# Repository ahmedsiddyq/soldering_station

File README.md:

# Soldering Station

DIY electronic soldering station project containing the hardware design, firmware, simulation files, and mechanical/laser-cut CAD files.

## Project Overview

This repository contains multiple development versions of a temperature-controlled soldering station:

- **LCD / digital soldering station** — PIC-based controller with temperature sensing, set-temperature input, PWM heater control, PI/PID-style control, UART, I²C, and display support.
- **Analog version** — earlier/full analog control design and PCB.
- **CAD / laser-cut parts** — enclosure and mechanical parts used for the station.
- **Simulation files** — Proteus project files for development and testing.

## Repository Structure

```text
soldering_station/
├── Full_anlog_uc38/
│   ├── circut/        # KiCad PCB/schematic
│   └── layout/        # Proteus/simulation and related files
├── lcd_ST/
│   ├── circut/        # KiCad schematic and PCB
│   └── firmware/
│       └── st_16f15223_irsegmet.X/
│           ├── main.c
│           ├── adc.c / adc.h
│           ├── display.c / display.h
│           ├── i2c1.c / i2c1.h
│           ├── pid.c / pid.h
│           ├── pwm.c / pwm.h
│           ├── timer_1ms.c / timer_1ms.h
│           ├── uart.c / uart.h
│           └── pin_deffiine.h
└── laser_cut_cad/
    └── *.lbrn2       # LightBurn CAD files
```

## LCD Soldering Station Firmware

The current firmware is written in C for a Microchip PIC16F1-series MCU and is developed with **MPLAB X / XC8**.

### Main firmware features

- 32 MHz internal oscillator
- Temperature ADC measurement
- Set-temperature ADC input
- 50-sample moving average
- 200 ms temperature-control period
- PWM heater control
- PI/PID-style temperature control
- Integral anti-windup
- 1 ms timer scheduling
- UART at 9600 baud
- I²C interface
- Numeric display
- Automatic display of the set temperature after a significant setpoint change

The main control loop collects ADC temperature samples into a 50-element buffer and calculates the average before updating the heater duty cycle.

### Current control parameters

```c
#define AVG_SAMPLES       50
#define PID_PERIOD_MS     200

#define S  20
#define KI 1
#define KP 5
```

PWM duty is limited to:

```text
0 ... 1000
```

## Pin Assignment

The current firmware pin map is documented in `pin_deffiine.h`.

| MCU Pin | Function |
|---|---|
| RA5 | Temperature ADC |
| RA4 | Temperature-set ADC |
| RC5 | Current sensing |
| RC4 | Heater PWM gate |
| RC2 | I²C SCL |
| RC1 | I²C SDA |
| RC0 | UART TX |
| RA2 | UART RX |
| RA1 | ICSPDAT |
| RA0 | ICSPCLK |

> Verify the exact MCU part number against the schematic and datasheet before building. Some existing firmware comments/configuration reference different PIC16F1522x/15225 variants.

## Firmware Build

Open:

```text
lcd_ST/firmware/st_16f15223_irsegmet.X
```

Development environment:

- MPLAB X IDE
- XC8 compiler
- PIC16F1522x device support package
- PICkit/programmer compatible with the selected MCU

The project contains the MPLAB X `nbproject` configuration and source files.

## Hardware Design

### LCD version

Located under:

```text
lcd_ST/circut/lcd_soldring_staion/
```

Main files:

- `lcd_soldring_staion.kicad_sch`
- `lcd_soldring_staion.kicad_pcb`

### Analog version

Located under:

```text
Full_anlog_uc38/circut/solder_staion/
```

Main files:

- `solder_staion.kicad_sch`
- `solder_staion.kicad_pcb`

## Simulation

Proteus simulation/development files are located in:

```text
Full_anlog_uc38/layout/
```

## Mechanical / Laser-Cut Design

Laser-cut enclosure/mechanical files are located in:

```text
laser_cut_cad/
```

The `.lbrn2` files can be opened with **LightBurn**.

## Development Status

This is an active DIY electronics project. Hardware, firmware, control parameters, and mechanical designs are still being developed and revised.

Current development includes:

- Temperature-control stability
- PI/PID tuning
- Temperature filtering
- Current sensing
- LCD/display interface
- PCB and enclosure development

## Safety

A soldering station contains a high-temperature heating element and may contain hazardous mains voltages depending on the power-supply design.

Use appropriate electrical isolation, fusing, grounding, thermal protection, over-temperature protection, enclosure, and strain relief.

Do not operate the heater unattended.

## License

No license has currently been specified for this repository. Unless a license is added, normal copyright restrictions apply to the repository contents.

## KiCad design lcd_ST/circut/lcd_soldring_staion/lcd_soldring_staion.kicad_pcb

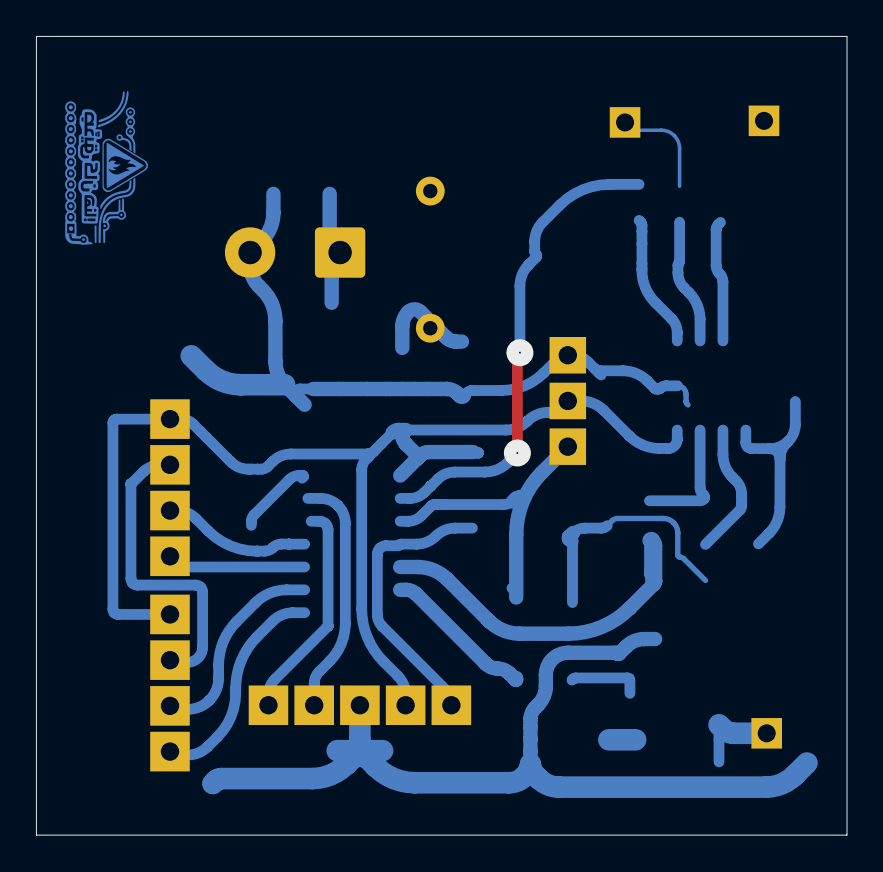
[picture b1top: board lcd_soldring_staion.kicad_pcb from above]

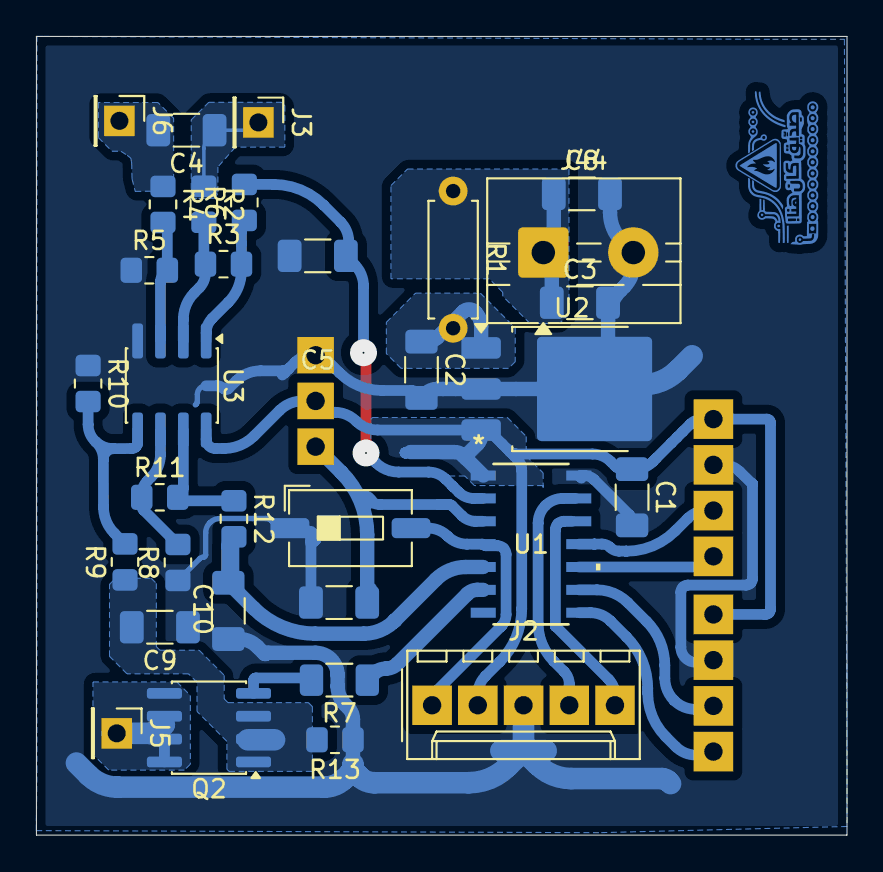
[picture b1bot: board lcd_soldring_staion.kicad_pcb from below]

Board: 2 copper layers, 45.0 x 44.4 mm, 35 parts (33 on the bottom side), 26 nets.

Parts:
C1: C; C_1206_3216Metric_Pad1.33x1.80mm_HandSolder
C2, C3: 2uf; C_1206_3216Metric_Pad1.33x1.80mm_HandSolder
C4, C5, C6, C8, C9, C10: 100nf; C_1206_3216Metric_Pad1.33x1.80mm_HandSolder
J2: Conn_01x05_Pin; Molex_KK-254_AE-6410-05A_1x05_P2.54mm_Vertical
J3, J5, J6: Conn_01x01_Pin; PinHeader_1x01_P2.54mm_Vertical
J7, J8: Conn_01x04_Pin; 01x04_fat_pins
J10: Conn_01x03_Pin; FanPinHeader_1x03_P2.54mm_Vertical
J44: Screw_Terminal_01x02; TerminalBlock_MaiXu_MX126-5.0-02P_1x02_P5.00mm
Q2: Si4162DY; SOIC-8_3.9x4.9mm_P1.27mm
R1: 50; R_Axial_DIN0207_L6.3mm_D2.5mm_P7.62mm_Horizontal
R2, R4, R6, R8, R9, R12, R13: 1K; R_0805_2012Metric_Pad1.20x1.40mm_HandSolder
R3, R5, R10, R11: 120K; R_0805_2012Metric_Pad1.20x1.40mm_HandSolder
R7: 0.02; R_1206_3216Metric_Pad1.30x1.75mm_HandSolder
SW1: SW_Push; SW_DIP_SPSTx01_Slide_6.7x4.1mm_W6.73mm_P2.54mm_LowProfile_J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
U1: PIC16F15223T-I/SL; SOIC14_SL_MCH
U2: L7805; TO-252-3_TabPin2
U3: LM358; SOIC-8_3.9x4.9mm_P1.27mm

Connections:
+24V: C3.1, C8.1, J44.1, R1.1
A: J2.4, U1.13 (RA0/ICSPDAT)
B: J2.5, U1.12 (RA1/ICSPCLK)
ClC: C6.1, J10.1, U1.3 (RA4)
unnamed: Q2.4 (G), R7.2
unnamed: R3.2, R6.1, U3.1
unnamed: R11.2, R12.1, U3.7
unnamed: C2.1, R1.2, U2.1 (IN)
unnamed: R4.2, R5.2, U3.3 (+)
unnamed: R2.2, R3.1, U3.2 (-)
unnamed: R9.2, R10.2, U3.5 (+)
unnamed: R8.2, R11.1, U3.6 (-)
RX: J8.1, U1.8 (RC2)
T+: C4.2, J6.1, R4.1
T-: C4.1, J3.1, R2.1
TEMP: C5.1, R6.2, U1.2 (RA5)
TX: J8.2, U1.9 (RC1)
VCC: C1.1, J2.2, J7.1, J8.4, J10.2, U1.1 (VDD), U2.3 (OUT), U3.8 (V+)
VPP: J2.1, SW1.2, U1.4 (*MCLR/VPP/RA3)
c+: C9.2, Q2.1 (S), Q2.2 (S), Q2.3 (S), R9.1, R13.2
c-: C1.2, C2.2, C3.2, C5.2, C6.2, C8.2, C9.1, C10.2, J2.3, J7.2, J8.3, J10.3, J44.2, R5.1, R8.1, R10.1, R13.1, SW1.1, U1.14 (VSS), U2.2 (GND), U3.4 (V-)
clk: J7.4, U1.10 (RC0)
current: C10.1, R12.2, U1.5 (RC5)
dat: J7.3, U1.11 (RA2)
heater: J5.1, Q2.5 (D), Q2.6 (D), Q2.7 (D), Q2.8 (D)
heater_gate: R7.1, U1.6 (RC4)

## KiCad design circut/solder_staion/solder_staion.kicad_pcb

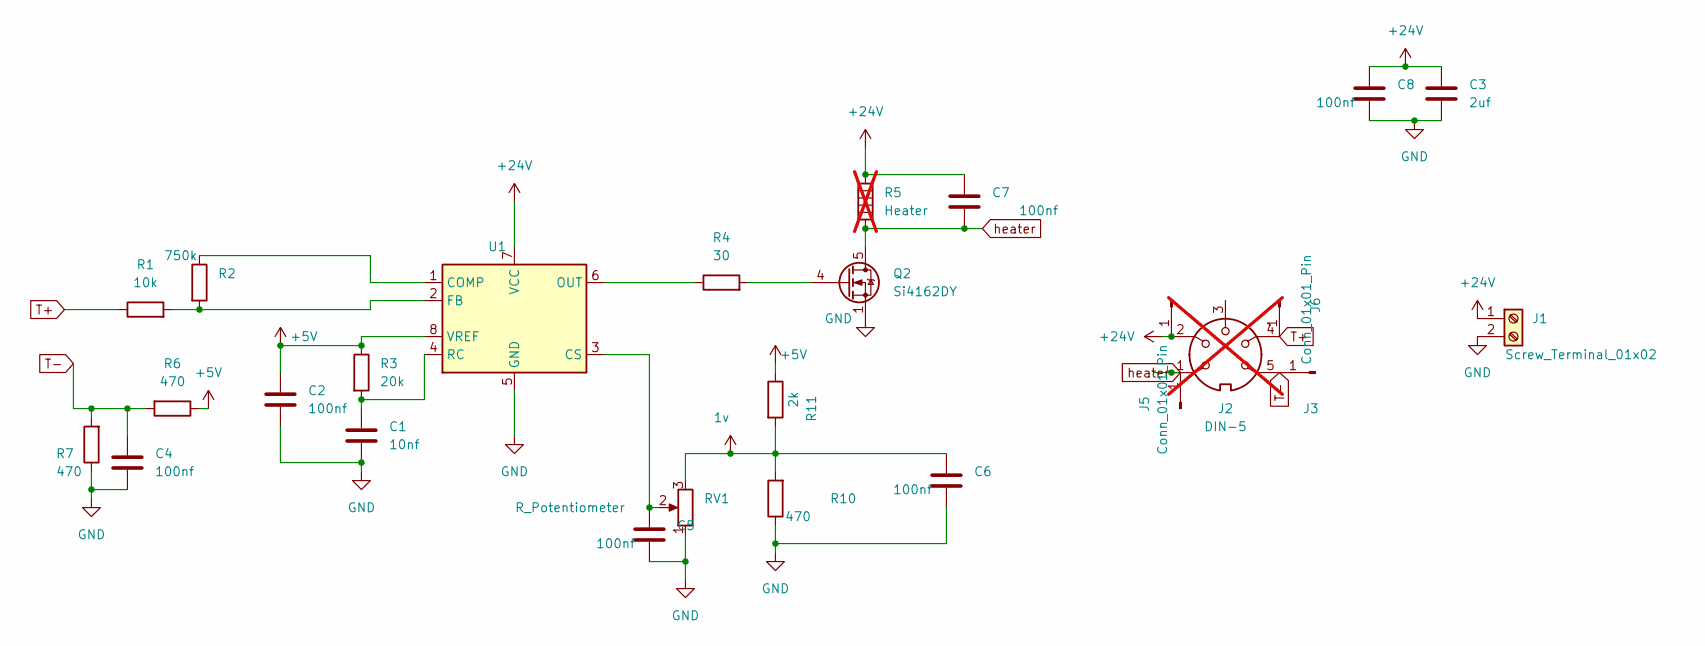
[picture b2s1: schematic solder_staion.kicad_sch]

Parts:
C1: 10nf; C_1206_3216Metric_Pad1.33x1.80mm_HandSolder
C2, C4, C5, C6, C7, C8: 100nf; C_1206_3216Metric_Pad1.33x1.80mm_HandSolder
C3: 2uf; C_1206_3216Metric_Pad1.33x1.80mm_HandSolder
J1: Screw_Terminal_01x02; TerminalBlock_MaiXu_MX126-5.0-02P_1x02_P5.00mm
J2: DIN-5; not fitted
J3: Conn_01x01_Pin; JST_XH_B1B-XH-AM_1x01_P2.50mm_Vertical
J4, J5, J6: Conn_01x01_Pin; PinHeader_1x01_P2.54mm_Horizontal
Q2: Si4162DY; SOIC-8_3.9x4.9mm_P1.27mm
R1: 10k; R_1206_3216Metric_Pad1.30x1.75mm_HandSolder
R2: 750k; R_1206_3216Metric_Pad1.30x1.75mm_HandSolder
R3: 20k; R_1206_3216Metric_Pad1.30x1.75mm_HandSolder
R4: 30; R_1206_3216Metric_Pad1.30x1.75mm_HandSolder
R5: Heater; not fitted
R6, R7, R10: 470; R_1206_3216Metric_Pad1.30x1.75mm_HandSolder
R11: 2k; R_1206_3216Metric_Pad1.30x1.75mm_HandSolder
RV1: R_Potentiometer; Potentiometer_ACP_CA9-H3,8_Horizontal
U1: UC3842_SOIC8; SOIC-8_3.9x4.9mm_P1.27mm

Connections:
1v: C6.1, R10.2, R11.2, RV1.3
+5V: C2.1, R3.1, R6.1, R11.1, U1.8 (VREF)
+24V: C3.1, C7.1, C8.1, J1.1, J2.2, J4.1, R5.1, U1.7 (VCC)
GND: C1.2, C2.2, C3.2, C4.2, C5.2, C6.2, C8.2, J1.2, Q2.1 (S), Q2.2 (S), Q2.3 (S), R7.1, R10.1, RV1.1, U1.5 (GND)
unnamed: Q2.4 (G), R4.2
unnamed: R2.1, U1.1 (COMP)
unnamed: C5.1, RV1.2, U1.3 (CS)
unnamed: R1.2, R2.2, U1.2 (FB)
unnamed: R4.1, U1.6 (OUT)
unnamed: C1.1, R3.2, U1.4 (RC)
T+: J2.4, J6.1, R1.1
T-: C4.1, J2.5, J3.1, R6.2, R7.2
heater: C7.2, J2.1, J5.1, Q2.5 (D), Q2.6 (D), Q2.7 (D), Q2.8 (D), R5.2

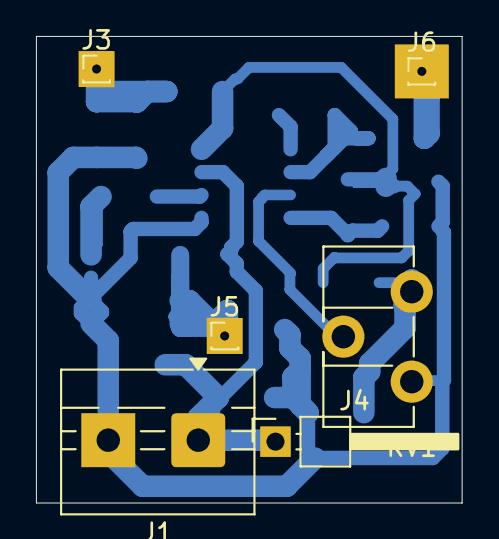
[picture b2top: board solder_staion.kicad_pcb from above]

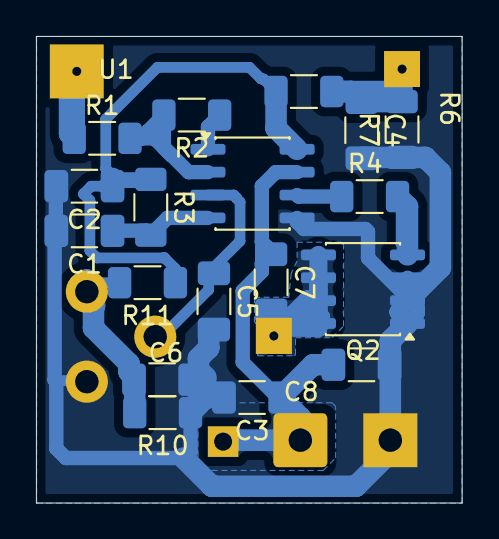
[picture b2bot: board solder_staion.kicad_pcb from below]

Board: 2 copper layers, 23.6 x 25.9 mm, 24 parts (18 on the bottom side), 13 nets.

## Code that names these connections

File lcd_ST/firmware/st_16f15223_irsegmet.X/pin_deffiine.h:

// PIC16F15223T-I/SL pin map (from schematic)
//
// RA5 (pin 2)  = TEMP
// RA4 (pin 3)  = temp_set
// RA3 (pin 4)  = MCLR/VPP
// RC5 (pin 5)  = current
// RC4 (pin 6)  = heater_gate
// RC3 (pin 7)  = not connected
// RC2 (pin 8)  = clk  -> I2C SCL
// RC1 (pin 9)  = dat  -> I2C SDA
// RC0 (pin 10) = TX
// RA2 (pin 11) = RX
// RA1 / RA0    = ICSPCLK / ICSPDAT (leave alone)

#define I2C1_SCL_TRIS   TRISCbits.TRISC2
#define I2C1_SDA_TRIS   TRISCbits.TRISC1
#define I2C1_SCL_ANSEL  ANSELCbits.ANSC2
#define I2C1_SDA_ANSEL  ANSELCbits.ANSC1


void pins(void)
{
    // =========================
    // GPIO direction
    // =========================
    TRISAbits.TRISA5 = 1;   // TEMP        = RA5, input
    TRISAbits.TRISA4 = 1;   // temp_set    = RA4, input

    TRISCbits.TRISC4 = 0;   // heater_gate = RC4, output
    TRISCbits.TRISC5 = 1;   // current     = RC5, input

    TRISCbits.TRISC0 = 0;   // TX          = RC0, output
    TRISAbits.TRISA2 = 1;   // RX          = RA2, input

    // RC3 is unconnected: drive it low as an output so it doesn't float
    LATCbits.LATC3   = 0;
    TRISCbits.TRISC3 = 0;


    // =========================
    // Analog / Digital
    // =========================
 
    ANSELAbits.ANSA5 = 1;   // TEMP
    ANSELAbits.ANSA4 = 1;   // temp_set
    ANSELAbits.ANSA2 = 0;   // RX

    ANSELCbits.ANSC5 = 1;   // current
    ANSELCbits.ANSC4 = 0;   // heater_gate
    ANSELCbits.ANSC3 = 0;   // unused
    ANSELCbits.ANSC0 = 0;   // TX
    I2C1_SCL_ANSEL   = 0;   // RC2 (SCL)
    I2C1_SDA_ANSEL   = 0;   // RC1 (SDA)


    // =========================
    // Unlock PPS
    // =========================

    PPSLOCK = 0x55;
    PPSLOCK = 0xAA;
    PPSLOCKbits.PPSLOCKED = 0;


    // =========================
    // UART1
    // =========================

    // TX1 -> RC0
    RC0PPS = 0x05;

    // RX1 <- RA2
    RXPPS = 0x02;
    
    
// PWM3 -> RC4 (heater_gate)
RC4PPS = 0x03;      // PWM3

    // =========================
    // I2C1
    // =========================

    // Both pins stay inputs; the MSSP drives them open-drain as needed
    I2C1_SCL_TRIS = 1;
    I2C1_SDA_TRIS = 1;

    // I2C inputs
    SSP1CLKPPS = 0x12;      // RC2 -> SCL1 input
    SSP1DATPPS = 0x11;      // RC1 -> SDA1 input

    // I2C outputs (must be on the same pins as the inputs)
    RC2PPS = 0x07;          // SCL1 -> RC2
    RC1PPS = 0x08;          // SDA1 -> RC1

    // Weak pull-ups (verify RC2I2C / RC1I2C exist on this device;
    // otherwise use WPUC, and prefer external resistors for real I2C)
WPUCbits.WPUC2 = 1;     // SCL (RC2)
WPUCbits.WPUC1 = 1;     // SDA (RC1)
    // =========================
    // Lock PPS
    // =========================

    PPSLOCK = 0x55;
    PPSLOCK = 0xAA;
    PPSLOCKbits.PPSLOCKED = 1;
}

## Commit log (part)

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2026-05-13 frist
2026-05-20 done_v1
2026-06-20 final v1
